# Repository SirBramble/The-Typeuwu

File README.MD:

# The Typeuwu

The Typeuwu is a modular keyboard design that can be extended with magnetic modules. It also provides a connector for a optional Bluetooth and Battery module.\
The firmware is written in C++ and provides a recompile free key remapping with the AniMacro scripting language.

## Hardware

The Typeuwu uses a RP2040 as the core processor, that polls the keyboard matrix, controls the LEDs and handles the communication between The keyboard and PC.

It also connects to the modules via magnetic pogo pin connectors located in the centre of each side. These provide the modules with power and expose the 5V level-shifted I2C lines.

Schematics can be found in ```/01 PCB/01 The Typeuwu PCB```.\
A PDF is available [```here```](01%20PCB/01%20The%20Typeuwu%20PCB/schematics/The%20Typeuwu.pdf).

## Firmware

The keyboard uses the custom written UWU (Universal Wordtyping Unit) Firmware that provides all needed interfaces for communicating with the Host and other modules.\
It also provides a parser for the 'AniMacro' scripting language, allowing the user to customise the key functionality from a config file located on the keyboards flash drive, without having to recompile the firmware.\

> [!IMPORTANT]  
> The firmware version included in this repository is deprecated. Though functional, further updates to the firmware will be posted to the [```UWU-Firmware```](https://github.com/SirBramble/UWU-Firmware) repository. Precompiled binary files are also available there.

### Uploading firmware

#### Precompiled firmware

To upload the precompiled binary, set the RP2040 into bootloader mode. This is done by first pressing the ```boot``` button, followed by either pressing the ```reset```button or performing a power cycle. The RP2040 should then mount as a flash drive named ```UF2```.\
Then either upload the Code using PIO or the Arduino IDE or copy the ```firmware.uf2``` file to the flash drive.

#### Compiling PIO

1. Make sure you have VSCode with the PlatformIO extension installed.
2. Clone the [```UWU-Firmware```](https://github.com/SirBramble/UWU-Firmware) repository (here: [github.com/SirBramble/UWU-Firmware](github.com/SirBramble/UWU-Firmware)).
3. Open the folder with PlatformIO.
   - PlatformIO should recognise it as a project and allow you to compile using either the VSCode interface or with the command ```platformio run```.
   - See [PlatformIO run documentation](https://docs.platformio.org/en/latest/core/userguide/cmd_run.html) for more information and possible arguments.
   - Any required library can either be added in the ```platformio.ini``` or copied to the ```lib``` (lib.h) and ```src``` (lib.c or lib.cpp) directory.

#### Compiling Arduino (deprecated)

1. Download the latest version of the Arduino IDE.
2. Install the [```arduino-pico```](https://github.com/earlephilhower/arduino-pico) board library.
    - You will also have to install the following librarys:
      - Adafruit NeoPixel (version: 1.12.0)
      - Adafruit SPIFlash (version: 4.3.1)
      - MIDI Library (version: 5.0.2)
3. Download the ```Typeuwu_Firmware``` folder.
4. Open the ```Typeuwu_Firmware.ino``` file with the Arduino IDE and either compile or upload directly.

## AniMacro scripting language

The 'AniMacro' scripting language allows the user to configure any Hardware Interface running the 'UWU firmware'.\
Configurations written in AniMacro are automatically loaded upon start-up and subsequently parsed using regular expressions. Additionally, the firmware can detect changes in the configuration file, facilitating its reload as needed, thereby enabling dynamic configuration adjustments at runtime.

A single configuration file accommodates configurations for various hardware UWU modules. The firmware selectively parses configurations pertinent to the currently connected hardware modules. This design choice allows for the seamless connection of multiple modules during runtime.

### Syntax

The 'AniMacro' syntax is based loosely on LaTeX syntax. A configuration for a specific module is wrapped in a ```begin``` and ```end``` qualifier:

```c
begin{module}
...
end{module}
```

Within a module configuration, multiple layers can be incorporated. Layers are a mechanism to implement diverse button configurations, facilitating dynamic switching between them at runtime. Layers can be added by typing ```Layer``` followed by the number of the layer:

```c
begin{module}
Layer x
...
end{module}
```

> [!IMPORTANT]
>By default the Firmware starts on layer 1. In the absence of a configured layer 1, the firmware remains inactive. It is advisable to consistently include a layer 1 configuration to ensure proper functionality.

All devices responsible for executing actions within a layer are designated using the ```Button``` keyword. Whether these devices are faders, potentiometers, or conventional buttons, they are uniformly referenced with the ```Button``` keyword.\
Buttons are implemented using the 'Button' keyword, followed by the button number, a colon, and a space. Subsequently, functionality can be added to the button by incorporating commands within the same line as the 'Button' keyword:

```c
begin{module}
Layer x
    Button a: commands
    Button b: commands
...
end{module}
```

Commands are categorized into several groups, which can be combined within a button configuration:

- Plain text:\
Entering plain text (e.g., "this is text123") utilizes the keyboard HID interface to type out the provided text.
    > [!NOTE]
    > Only ASCII characters are accepted in plain text. Non-ASCII characters (e.g. ```ä```) are managed with separate commands.
- ```\COMMAND``` with no arguments:\
    These commands serve as non-configurable placeholders for specific actions. For instance, pressing the 'Enter' key on the keyboard (```\ENTER_KEY```) or adding umlauts (```\ae``` => ```ä```).
- ```\COMMAND{}``` with arguments:\
    These commands are commonly employed to configure actions and callbacks within the firmware.\
    For example: ```\COLOR{const,green}``` would set the button to a constant green colour.\
    ```\MIDI_CC_KEY{16,1}\COLOR{midi,white}``` would configure a MIDI callback, binding the button to MIDI CC number 16 on MIDI channel 1. When the button is triggered, a MIDI message is dispatched to the host (PC), initiating an action. Subsequently, the host can relay back the state of the triggered action. The response from the host is then linked to the button colour, with a response greater than 126 denoting a triggered colour override, and a response of less than 126 signifying a reversion back to the layer default.

### List of commands

#### AniMacro commands

| Command | Description | Note |
| --- | --- | --- |
| Plain text | Types out the given text via the HID Interface | Only works with ASCII characters|
| ```\ae``` ```\oe``` ```\ue``` | Types out ```Umlauts``` (ä,ö,ü) | |
| ```\SZ_KEY``` | Sends keycode of ```ß``` key | |
| ```\GRAVE_KEY``` | Sends keycode of ```backtick``` ('´') key | |
| ```\CAPS_LOCK_KEY``` | Sends keycode of ```caps lock``` key | |
| ```\LSHIFT_KEY``` | Sends keycode of ```left shift``` key | |
| ```\RSHIFT_KEY``` | Sends keycode of ```right shift``` key | |
| ```\LCTRL_KEY``` | Sends keycode of ```left control``` key | For control combinations (e.g. ```CTRL``` + ```C```) refer to ```\STRG{char}```|
| ```\RCTRL_KEY``` | Sends keycode of ```right control``` key | For control combinations (e.g. ```CTRL``` + ```C```) refer to ```\STRG{char}```|
| ```\LATL_KEY``` | Sends keycode of ```left alt``` key | |
| ```\RATL_KEY```| Sends keycode of ```right alt``` key | |
| ```\WIN_KEY``` | Sends keycode of ```windows``` key | |
| ```\APP_KEY``` | Sends keycode of ```app``` key | |
| ```\RMETA_KEY``` | Sends keycode of ```right meta``` key | |
| ```\SPACE_KEY``` | Sends keycode of ```space bar``` key | Equivalent to typing space character in plain text |
| ```\BACKSPACE_KEY``` | Sends keycode of ```backspace``` key | |
| ```\DEL_KEY``` | Sends keycode of ```delete``` key | |
| ```ENTER_KEY``` | Sends keycode of ```enter``` key | |
| ```ESC_KEY``` | Sends keycode of ```escape``` key | |
| ```Tab_KEY``` | Sends keycode of ```tab``` key | |
| ```F[x]_KEY``` | Sends keycode of ```F[x]``` key | ```[x]``` to be replaced with number from ```1-12```|
| ```[arrow]_KEY``` | Sends keycode of ```[arrow]``` key | [arrow] to be replaced with one of: ```UP```, ```DOWN```, ```LEFT```, ```RIGHT```|
| ```[arrow]_KEY{[x]}```| Sends keycode of ```[arrow]``` key ```[x]``` times | ```[x]``` to be replaced with number and ```[arrow]``` to be replaced with one of: ```LEFT, RIGHT``` |
| ```\STRG{char}``` | Sends control combinations | Example: ```\STRG{c}``` => ```CTRL``` + ```C```|
| ```\MIDI_CC{[CT],[CH]}``` | Sends MIDI CC with number ```[CT]``` on MIDI channel ```[CH]``` with value from button | Replace ```[CT]``` with number from 0 to 127 and ```[CH]``` with number from 1-15. The button has to have a value or be a ```fader```/```potentiometer```/```encoder```.|
| ```\MIDI_CC_KEY{[CT],[CH]}``` | Sends MIDI CC with number ```[CT]``` on MIDI channel ```[CH]``` with value 127 | Replace ```[CT]``` with number from ```0``` to ```127``` and ```[CH]``` with number from ```1-15```. Used to trigger button events in software|
| ```\COLOR{[M],[C]}``` | Sets colour mode of button to ```[M]``` with colour ```[C]``` | Refer to ```colour mode list``` for valid mode ```[M]``` and ```colour list``` for valid colour ```[C]```|
| ```\COLOR{[M],[R],[G],[B]}``` | Sets colour mode of button to ```[M]``` with colour comprised of ```[R]```,```[G]``` and ```[B]``` | Refer to ```colour mode list``` for valid mode ```[M]```|
| ```\LAYER{[L]}``` | Sets active Layer to ```[L]``` | Layer ```[L]``` should be defined. Example: For ```\Layer{2}```, ```Layer 2``` should be defined.|

#### Colour mode list

|<div style="width:90px">Colour Mode</div> | Description | Note|
|:---|:---|:---|
| ```const``` | Sets a constant colour | |
| ```pressed``` | Sets the given colour if the button is triggered | |
| ```not pressed``` | Sets the given colour if the button is not triggered | |
| ```toggle``` | Toggles the colour on button trigger | |
| ```MIDI``` | Sets the colour based on message received over MIDI | Button has to be set as MIDI button with ```\MIDI_CC_KEY```. The channel and number set in ```\MIDI_CC_KEY``` will be used to trigger the colour|
| ```disabled``` | Disables the colour on the key | |

#### Colour list

|Colour|Note|
|:---|:---|
| ```red``` | |
| ```yellow``` | |
| ```green``` | |
|```cyan``` | |
| ```blue``` | |
| ```magenta``` | |
| ```white``` | |
| ```none/off``` | Used for modes, where colour is not a relevant parameter|

## Case

The Case for the Typeuwu is 3D-printed. Solidworks project files, STEP and STL files are included.

## Pictures

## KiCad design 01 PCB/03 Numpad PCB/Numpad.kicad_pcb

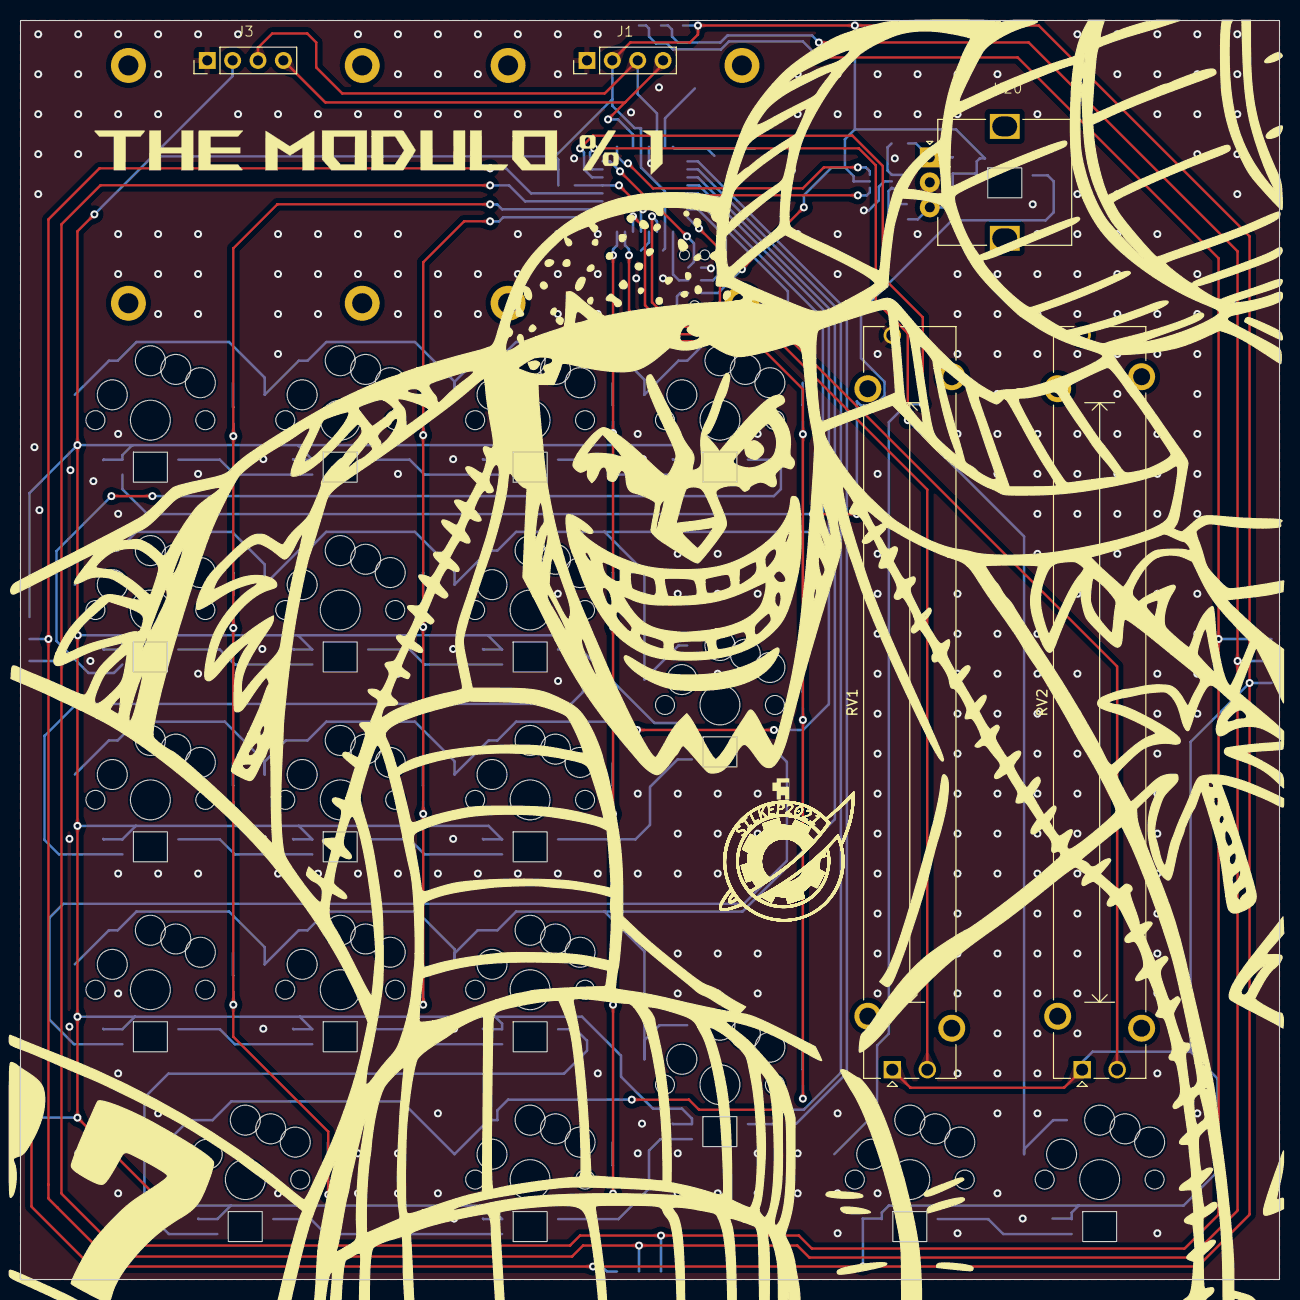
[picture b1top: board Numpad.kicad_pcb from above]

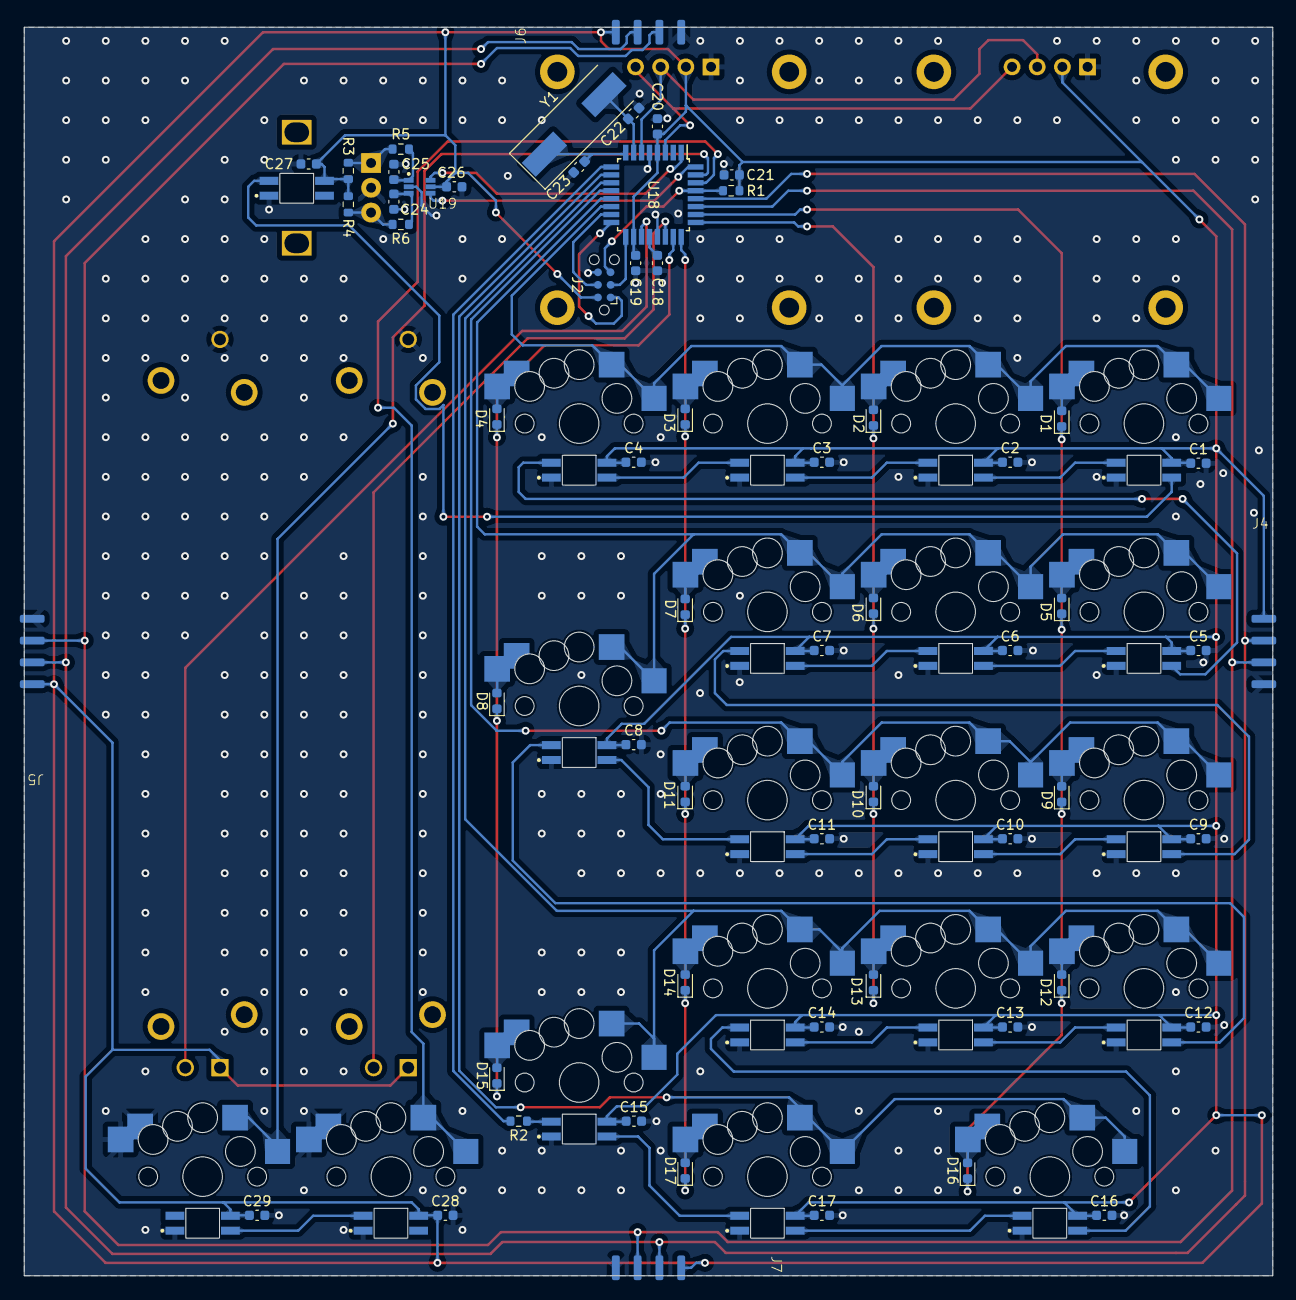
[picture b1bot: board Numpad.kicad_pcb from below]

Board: 2 copper layers, 126.0 x 126.0 mm, 84 parts (60 on the bottom side), 69 nets.

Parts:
C1, C2, C3, C4, C5, C6, C7, C8, C9, C10, C11, C12, C13, C14, C15, C16, C17, C18, C19, C20, C24, C25, C26, C27, C28, C29: 100nF; C_0603_1608Metric
C21: 1uF; C_0603_1608Metric
C22, C23: 22pF; C_0603_1608Metric
D1, D2, D3, D4, D5, D6, D7, D8, D9, D10, D11, D12, D13, D14, D15, D16, D17: D_Small; D_0603_1608Metric
J1: Display 1; MC096VX and SSD1306 Display module 0.96”
J2: AVR-ISP-6; Tag-Connect_TC2030-IDC-NL_2x03_P1.27mm_Vertical
J3: Display 2; MC096VX and SSD1306 Display module 0.96”
J4, J5, J6, J7: Conn_01x04; POGO Magnetic 4 Pin 2,2mm Horizontal
R1, R3, R4, R5, R6: 10k; R_0603_1608Metric
R2: 330; R_0603_1608Metric
RV1, RV2: PTA6043-2010CIB502; Potentiometer_Bourns_PTA6043_Single_Slide
U1, U2, U3, U4, U5, U6, U7, U9, U10, U11, U12, U13, U14, U17, U21, U22: Multi_Hotswap_with_RGB; Multi Hotswap with RGB 1U
U8, U15: Multi_Hotswap_with_RGB; Multi Hotswap with RGB 2U 90deg
U16: Multi_Hotswap_with_RGB; Multi Hotswap with RGB 2U
U18: ATmega328PB-A; TQFP-32_7x7mm_P0.8mm
U19: SN74LVC2G17DCKR
U20: Alps EC12 with Neopixel
Y1: ABLS-16.000MHZ-D-3-Y-T; Crystal_SMD_HC49-SD

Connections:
+5V: C1.1, C2.1, C3.1, C4.1, C5.1, C6.1, C7.1, C8.1, C9.1, C10.1, C11.1, C12.1, C13.1, C14.1, C15.1, C16.1, C17.1, C19.1, C20.1, C21.1, C26.1, C27.1, C28.1, C29.1, J1.2, J2.2 (VCC), J3.2, J4.4, J5.4, J6.4, J7.4, R1.1, R3.1, R4.1, RV1.1, RV2.1, U1.6 (VDD), U2.6 (VDD), U3.6 (VDD), U4.6 (VDD), U5.6 (VDD), U6.6 (VDD), U7.6 (VDD), U8.6 (VDD), U9.6 (VDD), U10.6 (VDD), U11.6 (VDD), U12.6 (VDD), U13.6 (VDD), U14.6 (VDD), U15.6 (VDD), U16.6 (VDD), U17.6 (VDD), U18.4 (VCC), U18.18 (AVCC), U19.5 (VCC), U20.4 (VDD), U21.6 (VDD), U22.6 (VDD)
COL_1: D1.1 (K), D5.1 (K), D9.1 (K), D12.1 (K), D16.1 (K), U18.26 (PC3)
COL_2: D2.1 (K), D6.1 (K), D10.1 (K), D13.1 (K), U18.25 (PC2)
COL_3: D3.1 (K), D7.1 (K), D11.1 (K), D14.1 (K), D17.1 (K), U18.24 (PC1)
COL_4: D4.1 (K), D8.1 (K), D15.1 (K), U18.23 (PC0)
DIN: R2.2, U18.9 (PD5)
DOUT_ENCODER: U1.5 (Dout), U20.1 (Din)
GND: C1.2, C2.2, C3.2, C4.2, C5.2, C6.2, C7.2, C8.2, C9.2, C10.2, C11.2, C12.2, C13.2, C14.2, C15.2, C16.2, C17.2, C18.2, C19.2, C20.2, C21.2, C22.2, C23.2, C24.2, C25.2, C26.2, C27.2, C28.2, C29.2, J1.1, J2.6 (GND), J3.1, J4.1, J5.1, J6.1, J7.1, RV1.3, RV2.3, U1.4 (GND), U2.4 (GND), U3.4 (GND), U4.4 (GND), U5.4 (GND), U6.4 (GND), U7.4 (GND), U8.4 (GND), U9.4 (GND), U10.4 (GND), U11.4 (GND), U12.4 (GND), U13.4 (GND), U14.4 (GND), U15.4 (GND), U16.4 (GND), U17.4 (GND), U18.5 (GND), U18.21 (GND), U19.2 (GND), U20.2 (GND), U20.C, U21.2, U21.4 (GND), U22.2, U22.4 (GND)
INT_0: U18.32 (PD2), U19.4 (2Y)
INT_1: U18.1 (PD3), U19.6 (1Y)
MISO: J2.1 (MISO), U18.16 (PB4)
MOSI: J2.4 (MOSI), U18.15 (PB3)
unnamed: D1.2 (A), U1.2
unnamed: D2.2 (A), U2.2
unnamed: D3.2 (A), U3.2
unnamed: D4.2 (A), U4.2
unnamed: D5.2 (A), U5.2
unnamed: D6.2 (A), U6.2
unnamed: D7.2 (A), U7.2
unnamed: D8.2 (A), U8.2
unnamed: D9.2 (A), U9.2
unnamed: D10.2 (A), U10.2
unnamed: D11.2 (A), U11.2
unnamed: D12.2 (A), U12.2
unnamed: D13.2 (A), U13.2
unnamed: D14.2 (A), U14.2
unnamed: D15.2 (A), U15.2
unnamed: D16.2 (A), U16.2
unnamed: D17.2 (A), U17.2
unnamed: R3.2, R5.2, U20.A
unnamed: R4.2, R6.2, U20.B
unnamed: U1.3 (Din), U2.5 (Dout)
unnamed: U2.3 (Din), U3.5 (Dout)
unnamed: U3.3 (Din), U4.5 (Dout)
unnamed: U4.3 (Din), U5.5 (Dout)
unnamed: U5.3 (Din), U6.5 (Dout)
unnamed: U6.3 (Din), U7.5 (Dout)
unnamed: U7.3 (Din), U9.5 (Dout)
unnamed: U10.3 (Din), U11.5 (Dout)
unnamed: U9.3 (Din), U10.5 (Dout)
unnamed: U8.5 (Dout), U11.3 (Din)
unnamed: U12.3 (Din), U13.5 (Dout)
unnamed: U8.3 (Din), U12.5 (Dout)
unnamed: U13.3 (Din), U14.5 (Dout)
unnamed: U14.3 (Din), U16.5 (Dout)
unnamed: R2.1, U15.3 (Din)
unnamed: U15.5 (Dout), U17.3 (Din)
unnamed: U16.3 (Din), U17.5 (Dout)
unnamed: C18.1, U18.20 (AREF)
unnamed: C25.1, R5.1, U19.1 (1A)
unnamed: C24.1, R6.1, U19.3 (2A)
unnamed: U21.3 (Din), U22.5 (Dout)
RESET: J2.5 (~RST), R1.2, U18.29 (~RESET/PC6)
ROW_1: U1.1, U2.1, U3.1, U4.1, U18.14 (PB2)
ROW_2: U5.1, U6.1, U7.1, U8.1, U18.13 (PB1)
ROW_3: U9.1, U10.1, U11.1, U18.12 (PB0)
ROW_4: U12.1, U13.1, U14.1, U15.1, U18.11 (PD7)
ROW_5: U16.1, U17.1, U18.10 (PD6)
SCK: J2.3 (SCK), U18.17 (PB5)
SCL_0: J4.3, J5.3, J6.3, J7.3, U18.28 (PC5)
SCL_1: J1.3, J3.3, U18.6 (PE1)
SDA_0: J4.2, J5.2, J6.2, J7.2, U18.27 (PC4)
SDA_1: J1.4, J3.4, U18.3 (PE0)
SLIDER_BUTTON_1: U18.30 (PD0), U21.1
SLIDER_BUTTON_2: U18.31 (PD1), U22.1
Slider_1: RV1.2, U18.22 (PE3)
Slider_2: RV2.2, U18.19 (PE2)
XTAL1: C22.1, U18.7 (XTAL1/PB6), Y1.2
XTAL2: C23.1, U18.8 (XTAL2/PB7), Y1.1

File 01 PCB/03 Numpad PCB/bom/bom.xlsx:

Ammount Boards: | 5
References | Value | Footprint | Manufacturer_Part_Number | Mouser Part Number | Quantity
C1, C2, C3, C4, C5, C6, C7, C8, C9, C10, C11, C12, C13, C14, C15, C16, C17, C18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 | 100nF | C_0603_1608Metric | CC0603KRX5R9BB104 | 603-CC603KRX5R9BB104 | 130
C22, C23 | 22pF | C_0603_1608Metric | 0201N220J500CT | 791-0201N220J500CT | 10
C21 | 1uF | C_0603_1608Metric | CL10A105KB8NNNC | 187-CL10A105KB8NNNC | 5
R1, R3, R4, R5, R6 | 10k | R_0603_1608Metric | CRT0603-FZ-1002ELF | 652-CRT0603FZ1002ELF | 25
R2 | 330 | R_0603_1608Metric | CR0603-FX-3300ELF | 652-CR0603FX-3300ELF | 5
D1, D2, D3, D4, D5, D6, D7, D8, D9, D10, D11, D12, D13, D14, D15, D16, D17 | D_Small | D_0603_1608Metric | RB521S30T5G | 863-RB521S30T5G | 85
U1, U2, U3, U4, U5, U6, U7, U9, U10, U11, U12, U13, U14, U17, U21, U22 | Multi_Hotswap_with_RGB | Multi Hotswap with RGB 1U | - | - | 80
U8, U15 | Multi_Hotswap_with_RGB | Multi Hotswap with RGB 2U 90deg | - | - | 10
U16 | Multi_Hotswap_with_RGB | Multi Hotswap with RGB 2U | - | - | 5
U18 | ATmega328PB-A | TQFP-32_7x7mm_P0.8mm | ATMEGA328PB-AU | 556-ATMEGA328PB-AU | 5
U19 | ~ | SN74LVC2G17DCKR | SN74LVC2G17DCKR | 595-SN74LVC2G17DCKR | 5
U20 | ~ | Alps EC12 with Neopixel | EC12E1220301 | 688-EC12E1220301 | 5
Y1 | ABLS-16.000MHZ-D-3-Y-T | Crystal_SMD_HC49-SD | ABLS-16.000MHZ-D-3-Y-T | 815-ABLS16000MHZD3YT | 5
RV1, RV2 | PTA6043-2010CIB502 | Potentiometer_Bourns_PTA6043_Single_Slide | PTA6043-2010CIB502 | 652-PTA6432010CIB502 | 10
J4, J5, J6, J7 | Conn_01x04 | POGO Magnetic 4 Pin 2,2mm Horizontal | - | - | 20
J1 | Display 1 | MC096VX and SSD1306 Display module 0.96” | - | - | 5
J2 | AVR-ISP-6 | Tag-Connect_TC2030-IDC-NL_2x03_P1.27mm_Vertical | - | - | 5
J3 | Display 2 | MC096VX and SSD1306 Display module 0.96” | - | - | 5

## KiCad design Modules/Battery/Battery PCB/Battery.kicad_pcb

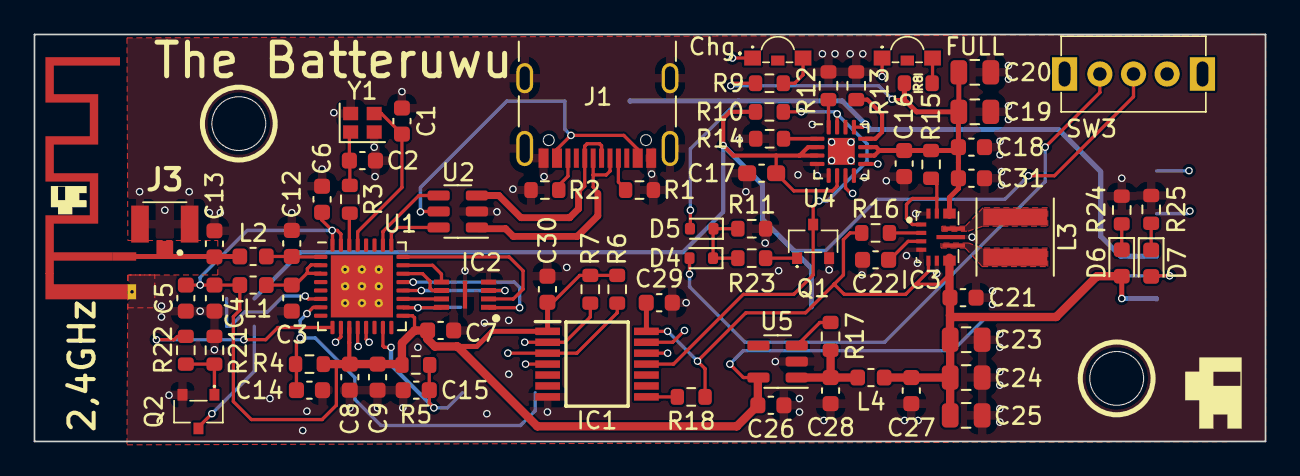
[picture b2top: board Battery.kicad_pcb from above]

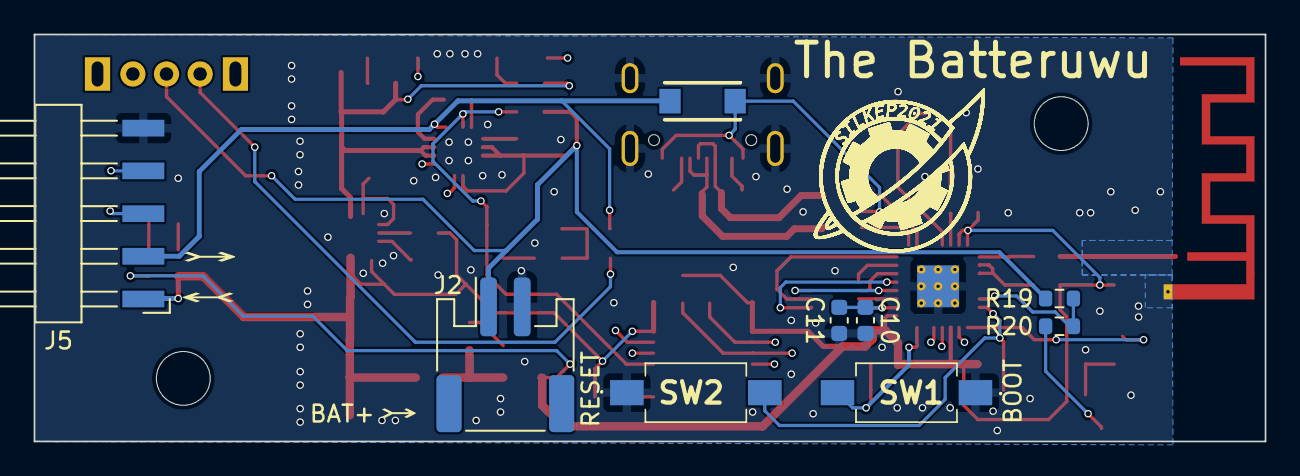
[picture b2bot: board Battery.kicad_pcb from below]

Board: 4 copper layers, 73.2 x 24.2 mm, 87 parts (9 on the bottom side), 58 nets.

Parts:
C1, C2: 10p; C_0603_1608Metric
C3, C4, C6, C7, C8, C11, C14, C15, C22, C27, C28, C29, C30, C31: 100n; C_0603_1608Metric
C5, C9, C10: 10u; C_0603_1608Metric
C12, C13: 3p3; C_0603_1608Metric
C16: 4.7 uF; C_0603_1608Metric
C17: 4.7 uF; C_0603_1608Metric_Pad1.08x0.95mm_HandSolder
C18, C21: 10uF; C_0603_1608Metric
C19, C20: 10uF; C_0805_2012Metric
C23, C24, C25: 22uF; C_0805_2012Metric
C26: 1u; C_0603_1608Metric
D1: CD214A-B240LR
D2: LED green; 155124RS73200
D3: LED red; 155124RS73200
D4, D5: RB21S30T5G; D_SOD-523
D6, D7: LED; LED_0603_1608Metric
H1, H2: MountingHole; MountingHole_3.2mm_M3_DIN965
IC1: LSF0204QPWRQ1; SOP65P640X120-14N
IC2: W25Q16JVUXIQ_TR; SON50P300X200X60-9N
IC3: TPS630701RNMR
J1: USB_C_Receptacle_USB2.0; USB_C_Receptacle_GCT_USB4105-xx-A_16P_TopMnt_Horizontal
J2: BATTERY; JST_PH_S2B-PH-SM4-TB_1x02-1MP_P2.00mm_Horizontal
J3: 2337019-1; 23370191
J5: M20-8900505; Harwin_M20-89005xx_1x05_P2.54mm_Horizontal
L1, L2, L4: 2n2; L_0603_1608Metric
L3: 1.5uH; EATON_EXL1V0402_4.6mmx4.6mm
Q1, Q2: T2N7002AK,LM; TBAT54CLM
R1, R2, R4, R5, R6, R7, R10: 5k1; R_0603_1608Metric
R3: 22; R_0603_1608Metric
R8, R9: 510; R_0603_1608Metric
R11, R14, R15, R17, R19, R21: 10k; R_0603_1608Metric
R12, R13: 1.18k; R_0603_1608Metric
R16: 100k; R_0603_1608Metric
R18, R22, R23, R24, R25: 1k; R_0603_1608Metric
R20: 22k; R_0603_1608Metric
SW1, SW2: PTS636 SP50; PTS636SP50SMTRLFS
SW3: POWER SWITCH; SLW-864547-5A-RA-D
U1: ESP32C3; QFN-32-1EP_5x5mm_P0.5mm_EP3.7x3.7mm_ThermalVias
U2: USBLC6-2SC6; SOT-23-6
U3: 2.4GHZ_PCB_Antenna_AN043; 2.4GHZ PCB Antenna AN043
U4: BQ24075RGT; VQFN-16-1EP_3x3mm_P0.5mm_EP1.6x1.6mm
U5: AP2112K-3.3; SOT-23-5
Y1: ECS-400-10-37B2-CKM-TR; Crystal_SMD_2016-4Pin_2.0x1.6mm

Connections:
5V CHRG: D1.1 (K), D5.2 (A), J5.2, U4.13 (IN)
+3V3: C4.1, C5.1, C6.1, C7.1, C8.1, C9.1, C26.1, C30.1, D7.2 (A), IC1.1 (VREF_A), L1.2, R4.2, R5.2, R6.2, R7.2, U1.11 (VDD3P3_RTC), U1.17 (VDD3P3_CPU), U1.31 (VDDA), U1.32 (VDDA), U5.5 (VOUT)
+5V: C21.1, C23.1, C24.1, C25.1, C27.1, C29.1, D6.2 (A), IC1.14 (VREF_B), IC3.5 (FB), IC3.7 (VOUT_1), IC3.8 (VOUT_2), J5.1, L4.1, R16.1, R18.1
/Power/CHG: D3.1 (K), U4.9 (~CHG)
/Power/DPPM OUT: C16.1, C18.1, C19.1, C20.1, C31.1, IC3.12 (VIN_1), IC3.13 (VIN_2), R8.1, R9.1, R15.1, U4.10 (OUT), U4.11 (OUT)
/Power/PGOOD: D2.1 (K), U4.7 (~PGOOD)
/Wireless/3V3 RF: C3.1, L1.1, U1.2 (VDD3P3), U1.3 (VDD3P3)
/Wireless/ANT_RF: C13.1, J3.1 (SIGNAL), L2.2, U3.1
/Wireless/BOOT: C15.1, R5.1, SW1.2, U1.15 (GPIO9)
/Wireless/CC1: J1.A5 (CC1), R1.1
/Wireless/CC2: J1.B5 (CC2), R2.1
/Wireless/EN_LS: IC1.8 (EN), R18.2
/Wireless/MCU_LNA: C12.1, L2.1, U1.1 (LNA_IN)
/Wireless/RESET: C14.1, R4.1, SW2.2, U1.7 (CHIP_EN)
/Wireless/VUSB: D1.2 (A), J1.A4 (VBUS), J1.A9 (VBUS), J1.B4 (VBUS), J1.B9 (VBUS), U2.5 (VBUS)
/Wireless/XTAL_N: C1.1, U1.29 (XTAL_N), Y1.3
/Wireless/XTAL_P: R3.1, U1.30 (XTAL_P)
/Wireless/XTAL_P_R: C2.1, R3.2, Y1.1
BAT+: C17.1, J2.1, R10.2, R19.1, SW3.2 (B), U4.2 (BAT), U4.3 (BAT), U4.6 (EN1)
ESP_DISABLE: IC1.4 (A3), U1.10 (MTDI)
GND: C1.2, C2.2, C3.2, C4.2, C5.2, C6.2, C7.2, C8.2, C9.2, C10.2, C11.2, C12.2, C13.2, C14.2, C15.2, C16.2, C17.2, C18.2, C19.2, C20.2, C21.2, C22.2, C23.2, C24.2, C25.2, C26.2, C27.2, C28.2, C29.2, C30.2, C31.2, IC1.7 (GND), IC2.4 (GND), IC2.9 (EP), IC3.4 (GND), IC3.6 (FB2), IC3.10 (PGND), IC3.15 (VSEL), J1.A1 (GND), J1.A12 (GND), J1.B1 (GND), J1.B12 (GND), J1.S1 (SHIELD), J2.2, J3.2 (GND_1), J3.3 (GND_2), J5.5, Q1.2 (S), Q2.2 (S), R1.2, R2.2, R11.2, R12.2, R13.2, R14.2, R21.2, R24.2, R25.2, SW1.1, SW2.1, U1.33 (EP), U2.2 (GND), U3.2, U4.4 (~CE), U4.5 (EN2), U4.8 (VSS), U4.17 (VSS), U5.2 (GND), Y1.2, Y1.4
MCU_D+: U1.26 (GPIO19), U2.4 (I/O2)
MCU_D-: U1.25 (GPIO18), U2.6 (I/O1)
unnamed: D2.2 (A), R8.2
unnamed: D3.2 (A), R9.2
unnamed: D4.2 (A), SW3.1 (A)
unnamed: D4.1 (K), D5.1 (K), R11.1, R23.1
unnamed: D6.1 (K), R24.1
unnamed: D7.1 (K), R25.1
unnamed: IC3.1 (PS/S), IC3.14 (EN), R15.2
unnamed: IC3.11 (L1), L3.1
unnamed: IC3.9 (L2), L3.2
unnamed: IC3.2 (PG), R16.2
unnamed: C22.1, IC3.3 (VAUX)
unnamed: Q1.1 (G), R23.2
unnamed: Q2.3 (D), R20.2
unnamed: Q2.1 (G), R21.1, R22.2
unnamed: R13.1, U4.12 (ILIM)
unnamed: R12.1, U4.16 (ISET)
unnamed: R17.2, U5.3 (EN)
unnamed: C28.1, L4.2, R17.1, U5.1 (VIN)
SCL_3V3: IC1.2 (A1), R7.1, U1.13 (MTDO)
SCL_5V: IC1.13 (B1), J5.4
SDA_3V3: IC1.3 (A2), R6.1, U1.12 (MTCK)
SDA_5V: IC1.12 (B2), J5.3
SPI_CLK: IC2.6 (CLK), U1.22 (SPICLK)
SPI_CS: IC2.1 (~CS), U1.21 (SPICS0)
SPI_DI: IC2.5 (DI(IO0)), U1.23 (SPID)
SPI_DO: IC2.2 (DO(IO1)), U1.24 (SPIQ)
SPI_HOLD: IC2.7 (IO3), U1.19 (SPIHD)
SPI_WP: IC2.3 (IO2), U1.20 (SPIWP)
SYSOFF: IC1.11 (B3), Q1.3 (D), R10.1, U4.15 (SYSOFF)
TS: R14.1, U4.1 (TS)
USB_D+: J1.A6 (D+), J1.B6 (D+), U2.3 (I/O2)
USB_D-: J1.A7 (D-), J1.B7 (D-), U2.1 (I/O1)
VDD SPI: C10.1, C11.1, IC2.8 (VCC), U1.18 (VDD_SPI)
V_SENSE: R19.2, R20.1, U1.6 (GPIO2)
V_SENSE_EN: R22.1, U1.9 (MTMS)

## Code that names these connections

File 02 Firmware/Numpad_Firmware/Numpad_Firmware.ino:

#include "Wire.h"
#include <Adafruit_NeoPixel.h>

#define MODULE_ADDRESS 0x20
#define I2C_BUFFER_SIZE 32

#define KEY_REMAPPING \
{ 1,  2,  3,  4},\
{ 5,  6,  7,  8},\
{ 9, 10, 11,  0},\
{12, 13, 14, 15},\
{16,  0, 17,  0},\

#define AMMOUNT_ROW 5
#define ROW1 10
#define ROW2 9
#define ROW3 8
#define ROW4 7
#define ROW5 6

#define AMMOUNT_COL 4
#define COL1 17
#define COL2 16
#define COL3 15
#define COL4 14

//--------ANALOG------------

#define PIN_SLIDER_BUTTON_1 0
#define PIN_SLIDER_BUTTON_2 1

#define PIN_SLIDER_1 26
#define PIN_SLIDER_2 25

#define ANALOG_DB 2
#define ADDITIONAL_ANALOG_ZERO_OFFSET 4

uint8_t slider1 = 0;
uint8_t slider2 = 0;

#define AMMOUNT_KEYS 23

int pins_row[AMMOUNT_ROW] = {ROW1, ROW2, ROW3, ROW4, ROW5};
int pins_col[AMMOUNT_COL] = {COL1, COL2, COL3, COL4};
uint8_t pressed[AMMOUNT_KEYS];

int diodeMatrixToKeyIndex[AMMOUNT_ROW][AMMOUNT_COL] = {KEY_REMAPPING};


#define IDLE 0x10
#define SEND_STATES 0x11

uint8_t mode = IDLE;

void receive_handler(int howMany);
void request_handler(void);

//------------------------Lighting-----------------------------
#define LED_PIN    5
#define LED_COUNT 23
#define LED_BRIGHTNESS 100

unsigned long pixelPrevious = 0;        // Previous Pixel Millis
unsigned long patternPrevious = 0;      // Previous Pattern Millis
int           patternCurrent = 0;       // Current Pattern Number
int           patternInterval = 5000;   // Pattern Interval (ms)
int           pixelInterval = 50;       // Pixel Interval (ms)
int           pixelQueue = 0;           // Pattern Pixel Queue
int           pixelCycle = 0;           // Pattern Pixel Cycle
uint16_t      pixelCurrent = 0;         // Pattern Current Pixel Number
uint16_t      pixelNumber = LED_COUNT;  // Total Number of Pixels

Adafruit_NeoPixel strip(LED_COUNT, LED_PIN, NEO_GRB + NEO_KHZ800);

void lightingSetup();
uint32_t Wheel(byte WheelPos);
void rainbow(uint8_t wait);

void setup() {
  delay(1000);
  pinMode(PIN_SLIDER_BUTTON_1, INPUT_PULLUP);
  pinMode(PIN_SLIDER_BUTTON_2, INPUT_PULLUP);

  Wire.begin(MODULE_ADDRESS);
  Wire.onRequest(request_handler);
  Wire.onReceive(receive_handler);
  //pinMode(A4, INPUT_PULLUP);
  //pinMode(A5, INPUT_PULLUP);
  lightingSetup();
  for(int i = 0; i < AMMOUNT_KEYS; i++){
    pressed[i] = 0;
  }
}

//int color = 255;

void loop() {
  update();
  rainbow(10);
  //if(!digitalRead(18)) strip.setPixelColor(1, strip.Color(255, 0, 0));
  //if(digitalRead(18)) strip.setPixelColor(1, strip.Color(0, 0, 0));
  //if(!digitalRead(19)) strip.setPixelColor(2, strip.Color(255, 0, 0));
  //if(digitalRead(19)) strip.setPixelColor(2, strip.Color(0, 0, 0));
  //strip.show();
  //strip.setPixelColor(10, strip.Color(0, map(analogRead(PIN_SLIDER_2), 0, 1023, 0, 255), 0));
  //strip.setPixelColor(1, strip.Color(0, color, 0));
  //color--;
  //if(color == 0) color = 255;
}

void update(){
  //Matrix
  for(int row = 0; row < AMMOUNT_ROW; row++){
    pinMode(pins_row[row], OUTPUT);
    delay(1);
    digitalWrite(pins_row[row], HIGH);
    delay(1);

    for(int col = AMMOUNT_COL - 1; col >= 0; col--){
      if(digitalRead(pins_col[col])){
        if(diodeMatrixToKeyIndex[row][col] != 0){
          pressed[diodeMatrixToKeyIndex[row][col] - 1] = 1;
        }
      }
      else{
        pressed[diodeMatrixToKeyIndex[row][col] - 1] = 0;
      }
    }
    delay(1);
    digitalWrite(pins_row[row], LOW);
    delay(1);
    pinMode(pins_row[row], INPUT);
    delay(1);
  }
  //Buttons slider
  pressed[17] = !digitalRead(PIN_SLIDER_BUTTON_1);
  pressed[18] = !digitalRead(PIN_SLIDER_BUTTON_2);

  //Slider
  if((map(analogRead(PIN_SLIDER_1), 0, 1023, 255, 0) >= (slider1 + ANALOG_DB)) || (map(analogRead(PIN_SLIDER_1), 0, 1023, 255, 0) <= (slider1 - ANALOG_DB))){
    slider1 = map(analogRead(PIN_SLIDER_1), 0, 1023, 255, 0);
  }
  if((map(analogRead(PIN_SLIDER_2), 0, 1023, 255, 0) >= (slider2 + ANALOG_DB)) || (map(analogRead(PIN_SLIDER_2), 0, 1023, 255, 0) <= (slider2 - ANALOG_DB))){
    slider2 = map(analogRead(PIN_SLIDER_2), 0, 1023, 255, 0);
  }
  
  if(map(analogRead(PIN_SLIDER_1), 0, 1023, 255, 0) < (ADDITIONAL_ANALOG_ZERO_OFFSET + ANALOG_DB)){
    slider1 = 0;
  }
  if(map(analogRead(PIN_SLIDER_2), 0, 1023, 255, 0) < (ADDITIONAL_ANALOG_ZERO_OFFSET + ANALOG_DB)){
    slider2 = 0;
  }

  if(map(analogRead(PIN_SLIDER_1), 0, 1023, 255, 0) > (255 - ADDITIONAL_ANALOG_ZERO_OFFSET + ANALOG_DB)){
    slider1 = 255;
  }
  if(map(analogRead(PIN_SLIDER_2), 0, 1023, 255, 0) > (255 - ADDITIONAL_ANALOG_ZERO_OFFSET + ANALOG_DB)){
    slider2 = 255;
  }
  pressed[19] = slider1;
  pressed[20] = slider2;
}

void receive_handler(int howMany){
  if(Wire.available()){
    mode = Wire.read();
  }
  if(mode == SEND_STATES) strip.setPixelColor(6, strip.Color(0, 255, 0));
  while(Wire.available()) Wire.read();
}

void request_handler(void){
  uint8_t i = 0;
  switch (mode) {
    case IDLE:
      //strip.setPixelColor(1, strip.Color(0, 255, 0));
      //strip.setPixelColor(2, strip.Color(0, 0, 0));
      //strip.setPixelColor(3, strip.Color(0, 0, 0));
      while(i < I2C_BUFFER_SIZE){
        Wire.write(0);
        i++;
      }
      break;
    case SEND_STATES:
      //strip.setPixelColor(1, strip.Color(0, 0, 0));
      //strip.setPixelColor(2, strip.Color(255, 0, 0));
      //strip.setPixelColor(3, strip.Color(0, 0, 0));
      while(i < AMMOUNT_KEYS){
        Wire.write(pressed[i]);
        //Wire.write(0);
        i++;
      }
      while(i < I2C_BUFFER_SIZE){
        Wire.write(0);
        i++;
      }
      //mode = IDLE;
      break;
    default:
      //strip.setPixelColor(1, strip.Color(0, 0, 0));
      //strip.setPixelColor(2, strip.Color(0, 0, 0));
      //strip.setPixelColor(3, strip.Color(0, 0, 255));
      while(i < I2C_BUFFER_SIZE){
        Wire.write(0);
        i++;
      }
      //mode = IDLE;
      break;
  }
}

void rainbow(uint8_t wait) {
  if(pixelInterval != wait)
    pixelInterval = wait;                   
  for(uint16_t i=0; i < pixelNumber; i++) {
    strip.setPixelColor(i, Wheel((i + pixelCycle) & 255)); //  Update delay time  
  }
  strip.show();                             //  Update strip to match
  pixelCycle++;                             //  Advance current cycle
  if(pixelCycle >= 256)
    pixelCycle = 0;                         //  Loop the cycle back to the begining
}

void lightingSetup(){
  strip.begin();           // INITIALIZE NeoPixel strip object (REQUIRED)
  strip.show();            // Turn OFF all pixels ASAP
  strip.setBrightness(LED_BRIGHTNESS); // Set BRIGHTNESS to about 1/5 (max = 255)
}

uint32_t Wheel(byte WheelPos) {
  WheelPos = 255 - WheelPos;
  if(WheelPos < 85) {
    return strip.Color(255 - WheelPos * 3, 0, WheelPos * 3);
  }
  if(WheelPos < 170) {
    WheelPos -= 85;
    return strip.Color(0, WheelPos * 3, 255 - WheelPos * 3);
  }
  WheelPos -= 170;
  return strip.Color(WheelPos * 3, 255 - WheelPos * 3, 0);
}

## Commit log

2023-07-21 Board V1
2023-07-26 Board V1 Rev 2
2025-01-14 added first module
2025-01-14 started Firmware
2025-01-14 started on filesystem
2025-01-14 code for key test
2025-01-14 bugfix
2025-01-14 firmware working version and 3D update
2025-01-14 started on Battery module
2025-01-14 update to I2C and MIDI Interface
2025-01-14 first rev of Battery module
2025-01-14 started battery firmware
2025-01-14 battery firmware done and updated Typeuwu firmware
    now supports more commands
2025-01-14 updated readme and cleanup
